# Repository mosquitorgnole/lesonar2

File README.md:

LeSonar 2
=========

We're directly selling our ultrasonic sonar development kit, and releasing it under an AGPL license so you can build projects on top of our sensor.

Links
-----
- [Main project link](https://tornyol.com/sonar)

Photos
------

Specifications
--------------

*   380x TDK Invensense T3902 PDM microphones.
*   Artix-7 A100T FPGA.
*   FT601Q parralel-to-usb bridge tested at up to 200MB/s.
*   32x 40khz Ultrasonic Piezoelectric emitters
*   2 free GPIOs

Capabilities
------------

### Active sonar

*   Optimized for 40KHz operation.
*   Up to 5°x5° beamwidth.
*   Range up to 8 meters depending on target sonar cross-section.

### Passive sonar

*   Can detect a bike air chamber leak at 3 meters.

Software
========

The sonar comes with two demoes
\- 2D Slicing camera, that shows the energyscape for a specific distance.
\- 3D Camera, that shows the reflected energy with a 3d point cloud.

Both examples are made with C99 C, using Raylib and Sokol for real-time 2D/3D visualization.

Attribution
======
The receiver hardware is based on the open-source [CP SoM One](https://github.com/controlpaths/cp_som_one)

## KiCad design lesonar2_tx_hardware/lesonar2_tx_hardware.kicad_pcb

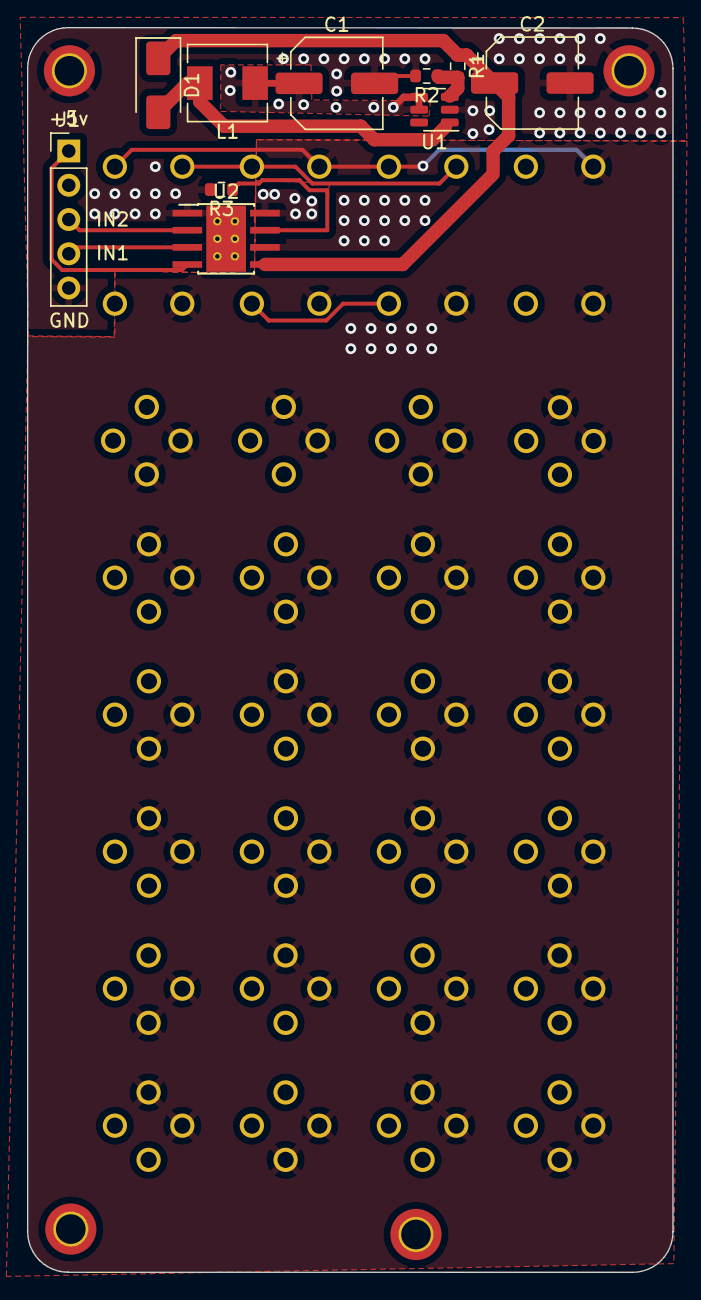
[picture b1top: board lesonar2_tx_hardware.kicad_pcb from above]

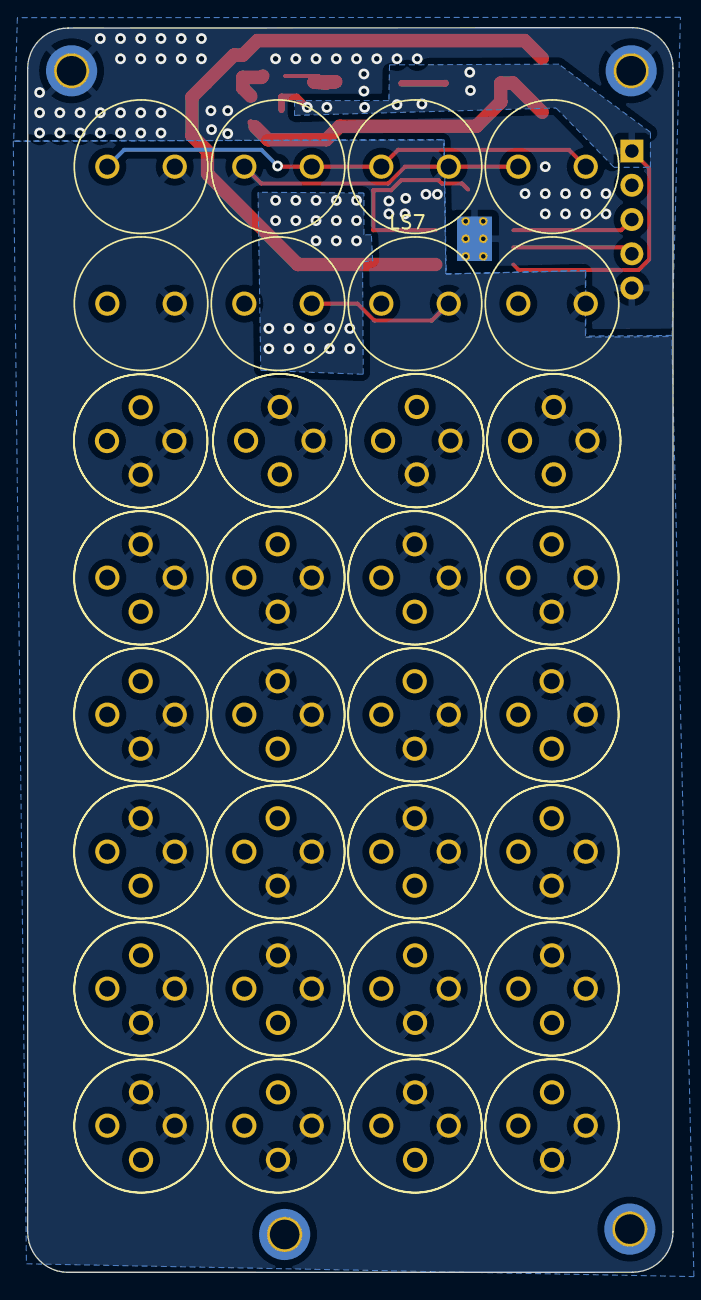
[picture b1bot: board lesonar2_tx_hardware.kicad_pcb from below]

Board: 2 copper layers, 47.9 x 92.3 mm, 70 parts (56 on the bottom side), 10 nets.

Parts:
C1, C2: 33uF; CP_Elec_6.3x5.4
D1: SS34; D_SMA
H2, H4, H5, H6: MountingHole_Pad; MountingHole_2.2mm_M2_DIN965_Pad_TopBottom
J1: Conn_01x05_Pin; PinHeader_1x05_P2.54mm_Vertical
L1: 22uH; L_Sunlord_MWSA0503S
LS1, LS2, LS3, LS4, LS5, LS6, LS7, LS8, LS9, LS10, LS11, LS12, LS13, LS14, LS15, LS16, LS17, LS18, LS19, LS20, LS21, LS22, LS23, LS24, LS25, LS26, LS27, LS28, LS29, LS30, LS31, LS32, LS73, LS74, LS75, LS75#2, LS76, LS76#2, LS77, LS78, LS79, LS79#2, LS80, LS80#2, LS81, LS82, LS83, LS83#2, LS84, LS84#2, LS85, LS86, LS87, LS87#2, LS88, LS88#2: MA40S4S; XDCR_MA40S4S
R1: 82k; R_0603_1608Metric
R2: 2k2; R_0603_1608Metric
R3: 0.2; R_0603_1608Metric
U1: MT3608; SOT-23-6
U2: DRV8870DDA; Texas_HTSOP-8-1EP_3.9x4.9mm_P1.27mm_EP2.95x4.9mm_Mask2.4x3.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

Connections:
+5V: C1.1, J1.1, L1.1, U1.4 (EN), U1.5 (IN), U2.4 (VREF)
+24V: C2.1, D1.1 (K), R1.1, U2.5 (VM)
GND: C1.2, C2.2, H2.1, H4.1, H5.1, H6.1, J1.5, R2.2, R3.2, U1.2 (GND), U2.1 (GND), U2.9 (GND)
unnamed: D1.2 (A), L1.2, U1.1 (SW)
unnamed: R1.2, R2.1, U1.3 (FB)
unnamed: R3.1, U2.7 (ISEN)
R6: J1.4, U2.3 (IN1)
TM: LS1.1, LS2.2, LS3.1, LS4.2, LS5.1, LS6.2, LS7.1, LS8.2, LS9.1, LS10.2, LS11.1, LS12.2, LS13.1, LS14.2, LS15.1, LS16.2, LS17.1, LS18.2, LS19.1, LS20.2, LS21.1, LS22.2, LS23.1, LS24.2, LS25.1, LS26.2, LS27.1, LS28.2, LS29.1, LS30.2, LS31.1, LS32.2, LS73.1, LS74.2, LS75.1, LS75#2.1, LS76.2, LS76#2.2, LS77.1, LS78.2, LS79.1, LS79#2.1, LS80.2, LS80#2.2, LS81.1, LS82.2, LS83.1, LS83#2.1, LS84.2, LS84#2.2, LS85.1, LS86.2, LS87.1, LS87#2.1, LS88.2, LS88#2.2, U2.6 (OUT1)
TP: LS1.2, LS2.1, LS3.2, LS4.1, LS5.2, LS6.1, LS7.2, LS8.1, LS9.2, LS10.1, LS11.2, LS12.1, LS13.2, LS14.1, LS15.2, LS16.1, LS17.2, LS18.1, LS19.2, LS20.1, LS21.2, LS22.1, LS23.2, LS24.1, LS25.2, LS26.1, LS27.2, LS28.1, LS29.2, LS30.1, LS31.2, LS32.1, LS73.2, LS74.1, LS75.2, LS75#2.2, LS76.1, LS76#2.1, LS77.2, LS78.1, LS79.2, LS79#2.2, LS80.1, LS80#2.1, LS81.2, LS82.1, LS83.2, LS83#2.2, LS84.1, LS84#2.1, LS85.2, LS86.1, LS87.2, LS87#2.2, LS88.1, LS88#2.1, U2.8 (OUT2)
U5: J1.3, U2.2 (IN2)

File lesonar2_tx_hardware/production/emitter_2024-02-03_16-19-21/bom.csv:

Designator,Footprint,Quantity,Value,LCSC Part #
"C1, C2",CP_Elec_6.3x5.4,2,33uF,C72508
D1,D_SMA,1,SS34 ,C8678
"H2, H4, H5, H6",MountingHole_2.2mm_M2_DIN965_Pad_TopBottom,4,MountingHole_Pad,DNP
J1,PinHeader_1x05_P2.54mm_Vertical,1,Conn_01x05_Pin,
L1,L_Sunlord_MWSA0503S,1,22uH,C718383
"LS1, LS10, LS11, LS12, LS13, LS14, LS15, LS16, LS17, LS18, LS19, LS2, LS20, LS21, LS22, LS23, LS24, LS25, LS26, LS27, LS28, LS29, LS3, LS30, LS31, LS32, LS4, LS5, LS6, LS7, LS73, LS74, LS75_2, LS75, LS76_2, LS76, LS77, LS78, LS79_2, LS79, LS8, LS80_2, LS80, LS81, LS82, LS83_2, LS83, LS84_2, LS84, LS85, LS86, LS87_2, LS87, LS88_2, LS88, LS9",XDCR_MA40S4S,56,MA40S4S,
R1,0603,1,82k,
R2,0603,1,2k2,
R3,0603,1,0.2,
U1,SOT-23-6,1,MT3608,C84817
U2,Texas_HTSOP-8-1EP_3.9x4.9mm_P1.27mm_EP2.95x4.9mm_Mask2.4x3.1mm_ThermalVias,1,DRV8870DDA,

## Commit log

2024-11-03 attribution
